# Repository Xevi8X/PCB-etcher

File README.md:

# PCB-etcher

This is the project of a small, but powerful thermostat based on ESP01 with phase controlled output and simple web application. Implements bang-bang controller with hysteresis, PID controller with anti-windup feature and autotune (hopefully, in future). Thermostat was design to control temperature in DIY PCB Etcher.

Project contains source code and electric circuit with PCB project, design in EAGLE PCB.

### Web application:

##### Info screen:

##### Charts:

##### Controller setting:

### Device:

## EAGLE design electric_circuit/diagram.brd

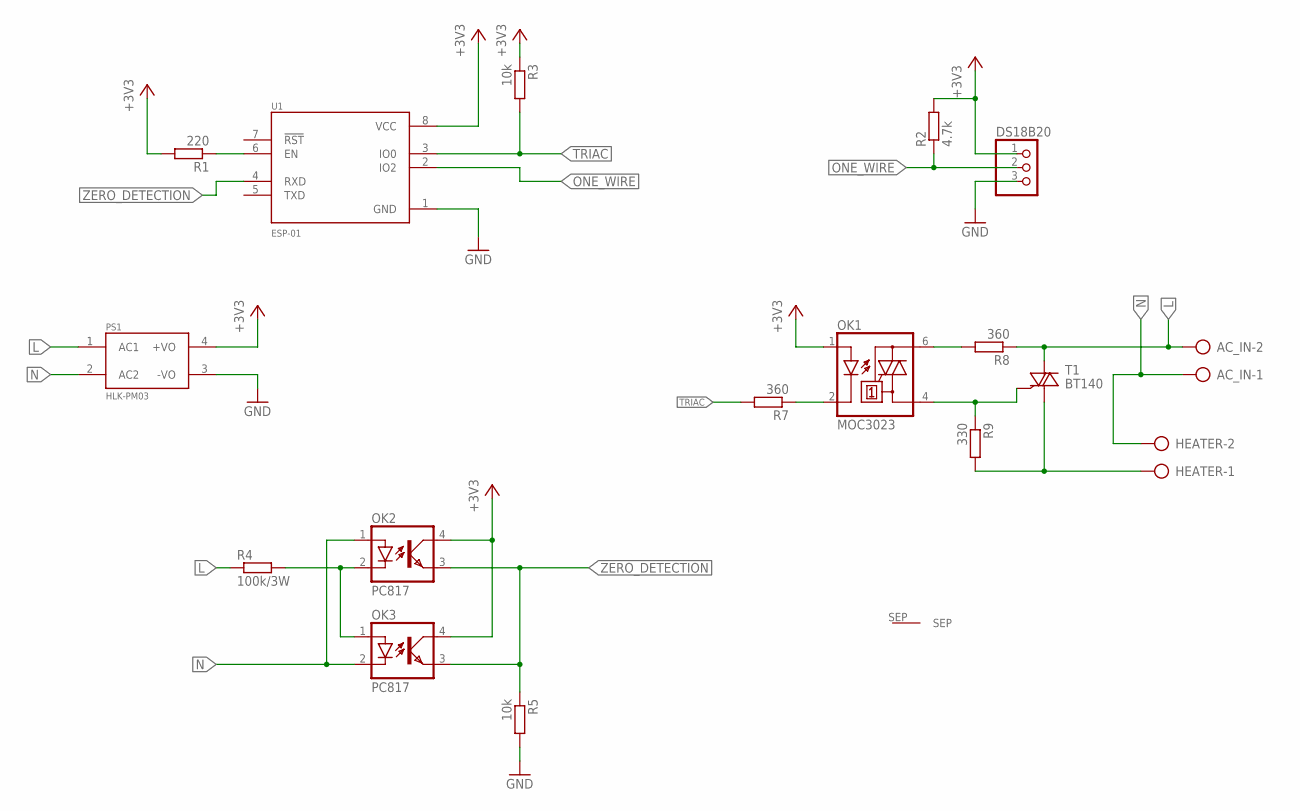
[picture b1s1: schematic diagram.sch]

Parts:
AC_IN: AK300/2
DS18B20: PINHD-1X3; 1X03
HEATER: AK300/2
OK1: MOC3023; DIL06
OK2, OK3: PC817; DIL04
PS1: HLK-PM03; CONV_HLK-PM03
R1: 220; R1206
R2: 4.7k; R1206
R3: 10k; 0204/5
R4: 100k/3W; 0414/15
R5: 10k; 0204/7
R7, R8: 360; M1206
R9: 330; M1206
T1: BT140; TO220BV
U1: ESP-01; XCVR_ESP8266-01/ESP-01
U$1: TEST; V7142

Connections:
+3V3: DS18B20.1, OK1.1 (A), OK2.4 (COL), OK3.4 (COL), PS1.4 (+VO), R1.2, R2.2, R3.1, U1.8 (VCC)
GND: DS18B20.3, PS1.3 (-VO), R5.2, U1.1 (GND)
L: AC_IN.2, PS1.1 (AC1), R4.1, R8.1, T1.T2 (A2)
N: AC_IN.1, HEATER.2, OK2.1 (A), OK3.2 (C), PS1.2 (AC2)
unnamed: R1.1, U1.6 (EN)
unnamed: OK2.2 (C), OK3.1 (A), R4.2
unnamed: OK1.6 (A2), R8.2
unnamed: OK1.4 (A1), R9.1, T1.G
unnamed: HEATER.1, R9.2, T1.T1 (A1)
unnamed: OK1.2 (C), R7.1
ONE_WIRE: DS18B20.2, R2.1, U1.2 (IO2)
TRIAC: R3.2, R7.2, U1.3 (IO0)
ZERO_DETECTION: OK2.3 (EMIT), OK3.3 (EMIT), R5.1, U1.4 (RXD)

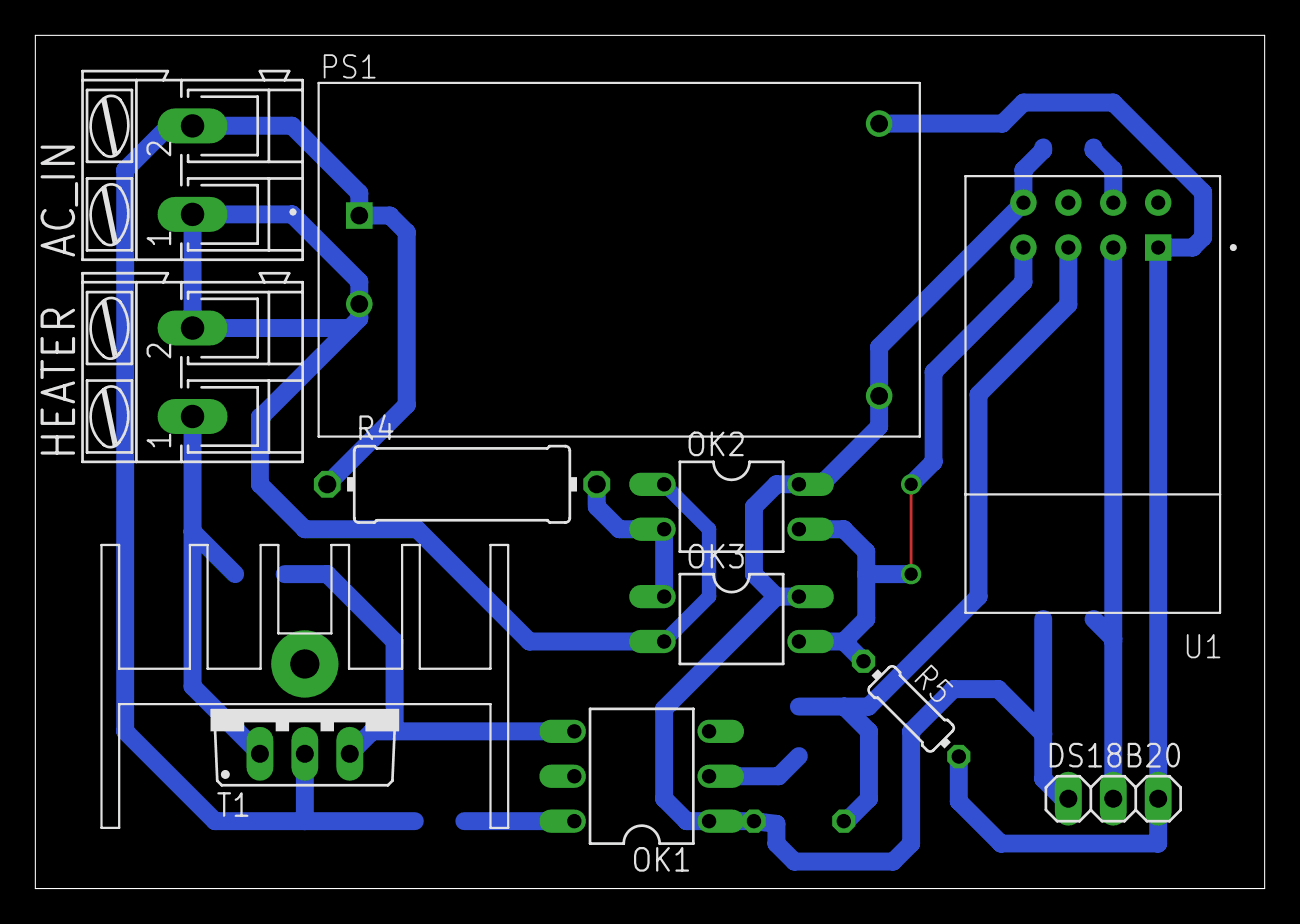
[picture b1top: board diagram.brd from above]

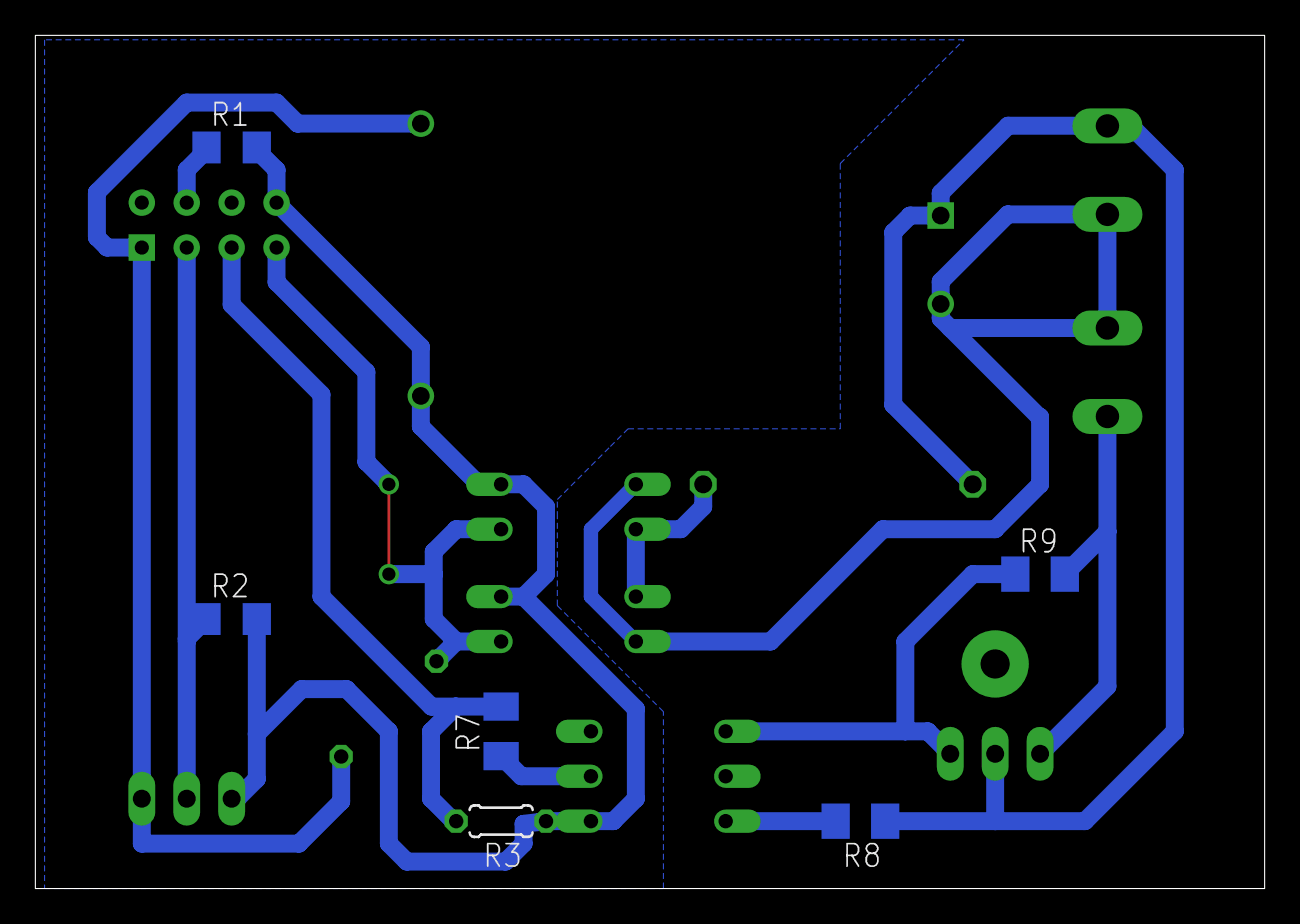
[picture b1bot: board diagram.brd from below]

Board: 2 copper layers, 69.5 x 48.2 mm, 18 parts (6 on the bottom side), 13 nets.

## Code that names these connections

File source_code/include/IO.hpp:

//Configuration
//==================================================
#define TRIAC_DELAY 3 //in ms, selected experimentally
//==================================================

//PINOUT
//==================================================
#define ONE_WIRE_PIN 2
#define TRIAC_PIN 0
#define ZERO_DETECTION_PIN 3
//==================================================

void IO_init();
void measure();

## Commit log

2023-02-12 JS refresh added.
2023-02-15 Zero crossing ISR and triac controll added
2023-02-15 Phase control and clean up!
2023-02-16 Selected triac delay and resolution
2023-02-17 Clean up
2023-02-20 PID controller added
2023-02-20 Overheat protection
2023-02-20 Temp chart
2023-02-20 Interval corection, exact power step
2023-02-20 quick controller switch part 1
2023-02-21 HTML upgrade
2023-02-21 Translate to EN
2023-02-21 Controller page
2023-02-21 Controller page communication
2023-02-21 Electric circuit with PCB project (EAGLE PCB)
2023-02-25 Anti-widnup added!
2023-02-25 Tuning pi controller - relay method
2023-02-26 Disable I action when error is too large
2023-02-26 EEPROM for controller params
